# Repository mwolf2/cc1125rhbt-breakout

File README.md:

# cc1125rhbt-breakout
410-480MHz CC1125RHBT breakout board with an SMA connector for antennas and 50 ohm traces. The component values can be varied to vary operating frequency. BRD/SCH are EAGLE board and schematic files, respectively. CAMOutputs contains XLN and Gerber files.

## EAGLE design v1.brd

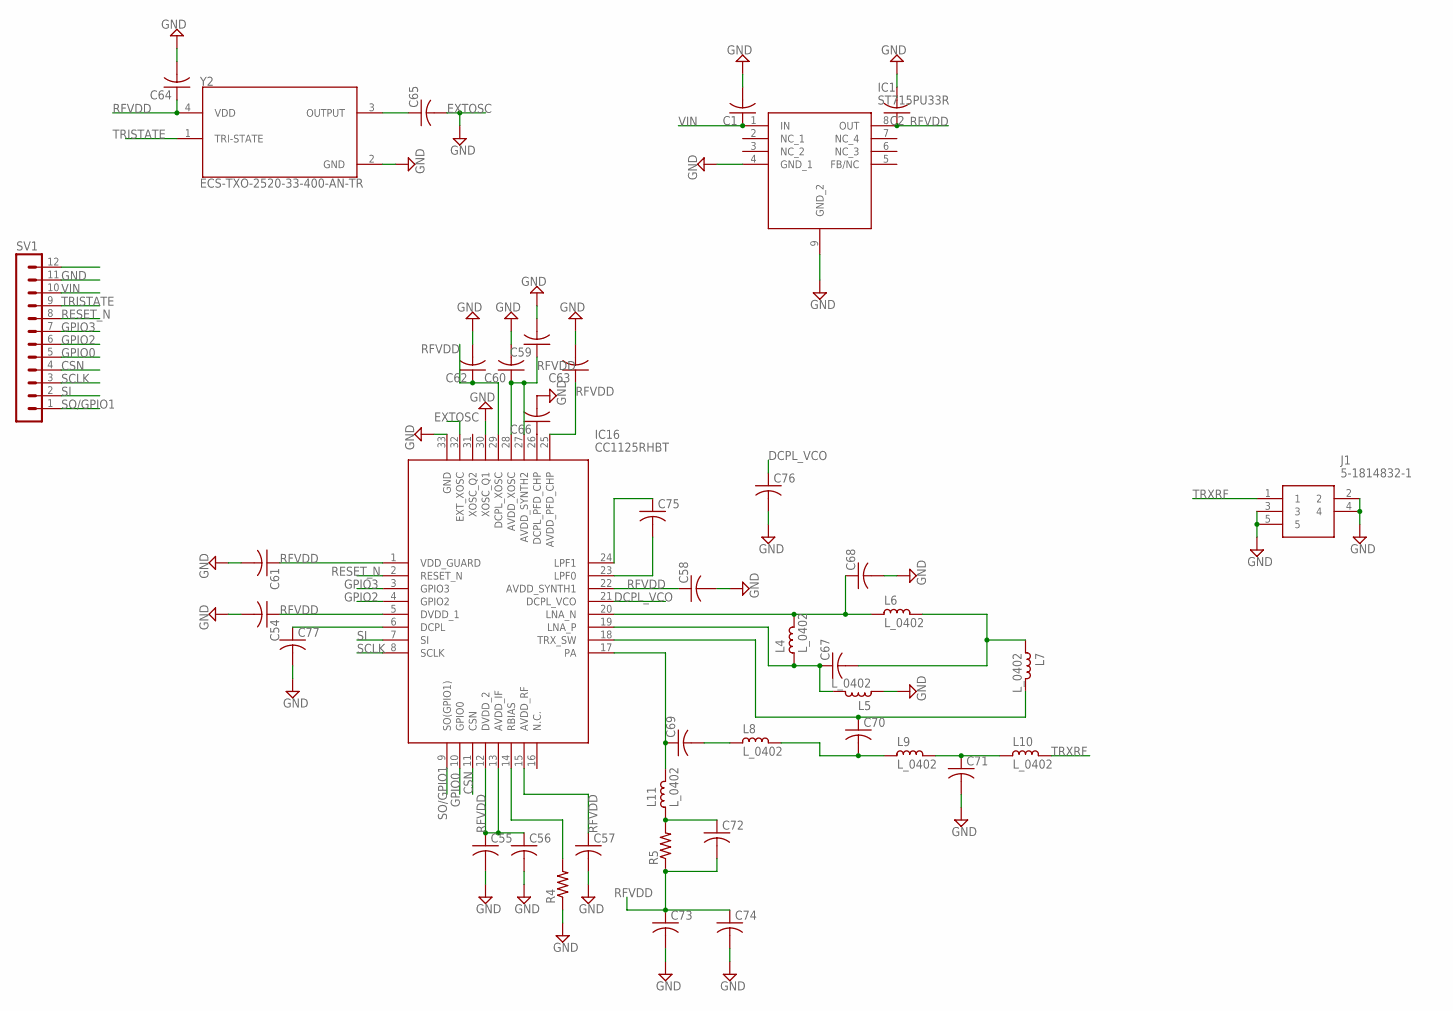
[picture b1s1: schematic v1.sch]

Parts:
C1, C2, C54, C55, C56, C58, C59, C60, C62, C65, C66, C67, C68, C69, C70, C71, C72, C73, C74, C75, C76, C77: C-USC0402; C0402
C57, C61, C63, C64: C-USC0805; C0805
IC1: ST715PU33R; SON65P300X300X100-9N
IC16: CC1125RHBT; QFN50P500X500X100-33N
J1: 5-1814832-1
L4, L5, L6, L7, L8, L9, L10, L11: L_0402; L0402
R4, R5: R-US_R0402; R0402
SV1: MA12-1
Y2: ECS-TXO-2520-33-400-AN-TR; OSC_ECS-TXO-2520-33-400-AN-TR

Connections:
CSN: IC16.11 (CSN), SV1.4
DCPL_VCO: C76.1, IC16.21 (DCPL_VCO)
EXTOSC: C65.2, IC16.32 (EXT_XOSC)
GND: C1.2, C2.2, C54.2, C55.2, C56.2, C57.2, C58.2, C59.2, C60.2, C61.2, C62.2, C63.2, C64.2, C66.2, C68.2, C71.2, C73.2, C74.2, C76.2, C77.2, IC1.4 (GND_1), IC1.9 (GND_2), IC16.30 (XOSC_Q1), IC16.33 (GND), J1.2, J1.3, J1.4, J1.5, L5.2, R4.1, SV1.11, Y2.2 (GND)
GPIO0: IC16.10 (GPIO0), SV1.5
GPIO2: IC16.4 (GPIO2), SV1.6
GPIO3: IC16.3 (GPIO3), SV1.7
unnamed: IC16.14 (RBIAS), R4.2
unnamed: C65.1, Y2.3 (OUTPUT)
unnamed: C66.1, IC16.26 (DCPL_PFD_CHP)
unnamed: C68.1, IC16.20 (LNA_N), L4.1, L6.2
unnamed: C67.1, IC16.19 (LNA_P), L4.2, L5.1
unnamed: C67.2, L6.1, L7.2
unnamed: C70.1, IC16.18 (TRX_SW), L7.1
unnamed: C69.1, IC16.17 (PA), L11.1
unnamed: C69.2, L8.2
unnamed: C70.2, L8.1, L9.2
unnamed: C71.1, L9.1, L10.2
unnamed: C72.1, L11.2, R5.2
unnamed: C77.1, IC16.6 (DCPL)
unnamed: C75.2, IC16.23 (LPF0)
unnamed: C75.1, IC16.24 (LPF1)
RESET_N: IC16.2 (RESET_N), SV1.8
RFVDD: C2.1, C54.1, C55.1, C56.1, C57.1, C58.1, C59.1, C60.1, C61.1, C62.1, C63.1, C64.1, C72.2, C73.1, C74.1, IC1.8 (OUT), IC16.1 (VDD_GUARD), IC16.5 (DVDD_1), IC16.12 (DVDD_2), IC16.13 (AVDD_IF), IC16.15 (AVDD_RF), IC16.22 (AVDD_SYNTH1), IC16.25 (AVDD_PFD_CHP), IC16.27 (AVDD_SYNTH2), IC16.28 (AVDD_XOSC), IC16.29 (DCPL_XOSC), R5.1, Y2.4 (VDD)
SCLK: IC16.8 (SCLK), SV1.3
SI: IC16.7 (SI), SV1.2
SO/GPIO1: IC16.9 (SO(GPIO1)), SV1.1
TRISTATE: SV1.9, Y2.1 (TRI-STATE)
TRXRF: J1.1, L10.1
VIN: C1.1, IC1.1 (IN), SV1.10

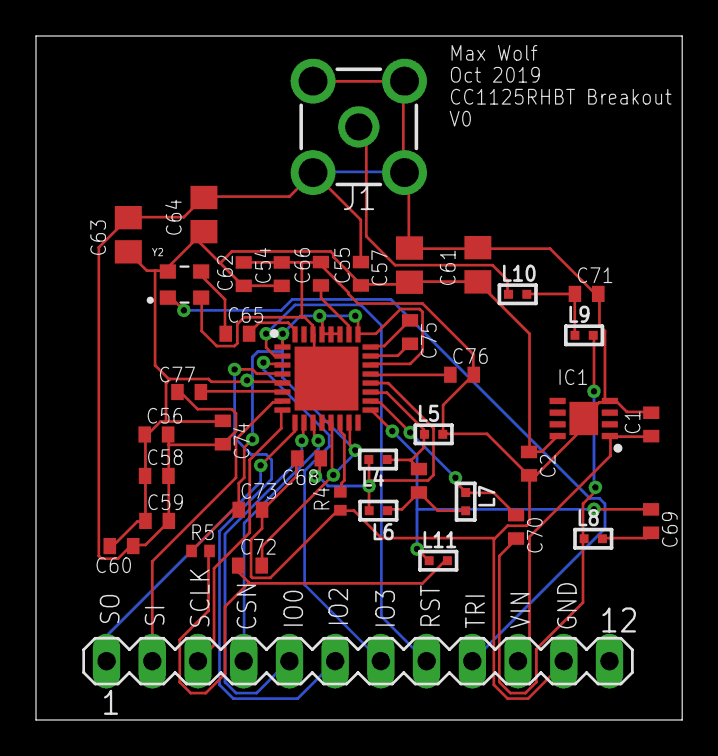
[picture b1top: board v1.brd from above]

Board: 4 copper layers, 35.9 x 38.0 mm, 41 parts (0 on the bottom side), 30 nets.

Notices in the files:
parts and their libraries:
rc-master-smd: Copyright (C) 2007, Bob Starr
